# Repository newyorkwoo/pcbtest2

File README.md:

# aipcb：由 Claude 驅動的本機 EDA

用自然語言描述電路，Claude 撰寫 `design.yaml`。之後的原理圖、元件庫、物理式擺放、自動佈線、GND 鋪銅、SPICE 模擬、ERC/DRC、送廠審核與 Gerber 輸出，全部在本機自動完成，不需要連網。

## 需求
- KiCad 10（`/Applications/KiCad`），本系統使用它的 kicad-cli、元件庫與 libngspice
- Python 3.12 虛擬環境：`uv venv --python 3.12 .venv && uv pip install --python .venv/bin/python numpy pyyaml mcp PySide6-Essentials`

## 使用方式
| 方式 | 指令 |
|---|---|
| 在 Claude Code 中對話 | 在本資料夾開啟 Claude Code，`.mcp.json` 會自動載入 `aipcb` 工具，例如輸入「幫我設計…」或「審核 fm_radio 能否送廠」 |
| 桌面儀表板 | `.venv/bin/python -m aipcb gui fm_radio` |
| 命令列全流程 | `.venv/bin/python -m aipcb build fm_radio` |
| 送廠檔 | `.venv/bin/python -m aipcb fab fm_radio`（AI 審核 PASS 才放行；`--force` 僅限打樣） |

## 流程
`design.yaml` → 元件庫（含 AI 自訂元件）→ 規格驗證 → 原理圖 → ERC → 物理擺放（力導向 + 模擬退火 + 合法化）→ 佈線（雙層 A*、拆線重佈、GND 扇出）→ PCB → DRC（含鋪銅連通性的閉迴路修補）→ SPICE 模擬 → 設計檢查 → 預覽 → **Claude 審核** → 送廠檔

詳細的設計與審核規範見 `CLAUDE.md`。範例專案位於 `projects/fm_radio/`。

## 專案與電路圖
每次建置（`previews` 階段）都會自動更新各專案的 `README.md` 與 `docs/`：原理圖 PDF / SVG、PCB 3D 圖、檢查與審核摘要。

| 專案 | 說明 | 電路圖 |
|---|---|---|
| [fm_radio](projects/fm_radio/) | FM/藍牙口袋收音機（ESP32 + RDA5807M + PAM8302，USB-C 充電） | [PDF](projects/fm_radio/docs/fm_radio_schematic.pdf) · [SVG](projects/fm_radio/docs/schematic.svg) |
| [outdoor_hmi](projects/outdoor_hmi/) | Outdoor Hub Board 2：按鍵、旋鈕、SOS、震動馬達與 2.5 W 喇叭 | [PDF](projects/outdoor_hmi/docs/outdoor_hmi_schematic.pdf) · [SVG](projects/outdoor_hmi/docs/schematic.svg) |

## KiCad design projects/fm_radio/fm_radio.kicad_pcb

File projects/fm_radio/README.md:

# FM/BT Pocket Radio

> 本檔由 `python -m aipcb previews` 自動產生，請勿手動編輯；設計來源是 `design.yaml`。

| 項目 | 內容 |
|---|---|
| 板子尺寸 | 80 × 60 mm，2 層，厚 1.6 mm |
| 零件 / 網路 | 72 顆 / 49 個 |
| DRC | 0 錯誤、0 未連接 |
| 自動檢查 | 通過（error 0、warning 47） |
| SPICE 模擬 | 4/4 通過 |
| AI 審核 | **CONDITIONAL**（2026-11-13T12:46:02） |

## 電路圖 Schematic

可放大的向量版：[docs/fm_radio_schematic.pdf](docs/fm_radio_schematic.pdf)

## PCB

## AI 審核摘要

依上一版審核的建議完成換件：電源路徑改為 LTC4412 + AO3401A 理想二極體（拔除 USB 時的 9 ms 掉壓消失，模擬已驗證），CR1220 電池座改為 LCSC 有貨的 Keystone 3000，其餘缺料號的零件都補上已確認的 LCSC 料號。重建結果：ERC 0、DRC 0/0、幾何檢查通過、模擬 4/4 通過。PCB 可打樣。唯一未解決的是 U6 RDA5807M 在 LCSC 沒有料，需另外採購或手焊，所以仍判定「有條件通過」。

- **[WARNING] U6 RDA5807M 沒有 LCSC 料號**
- **[WARNING] 電池低於約 3.33 V 時 3.3 V 軌脫離穩壓（模擬 02）**
- **[WARNING] OLED 模組腳位順序因廠商而異**
- **[WARNING] VSYS 有 3.2 mm 走線縮到 0.2 mm**

完整審核內容：[out/review.md](out/review.md)

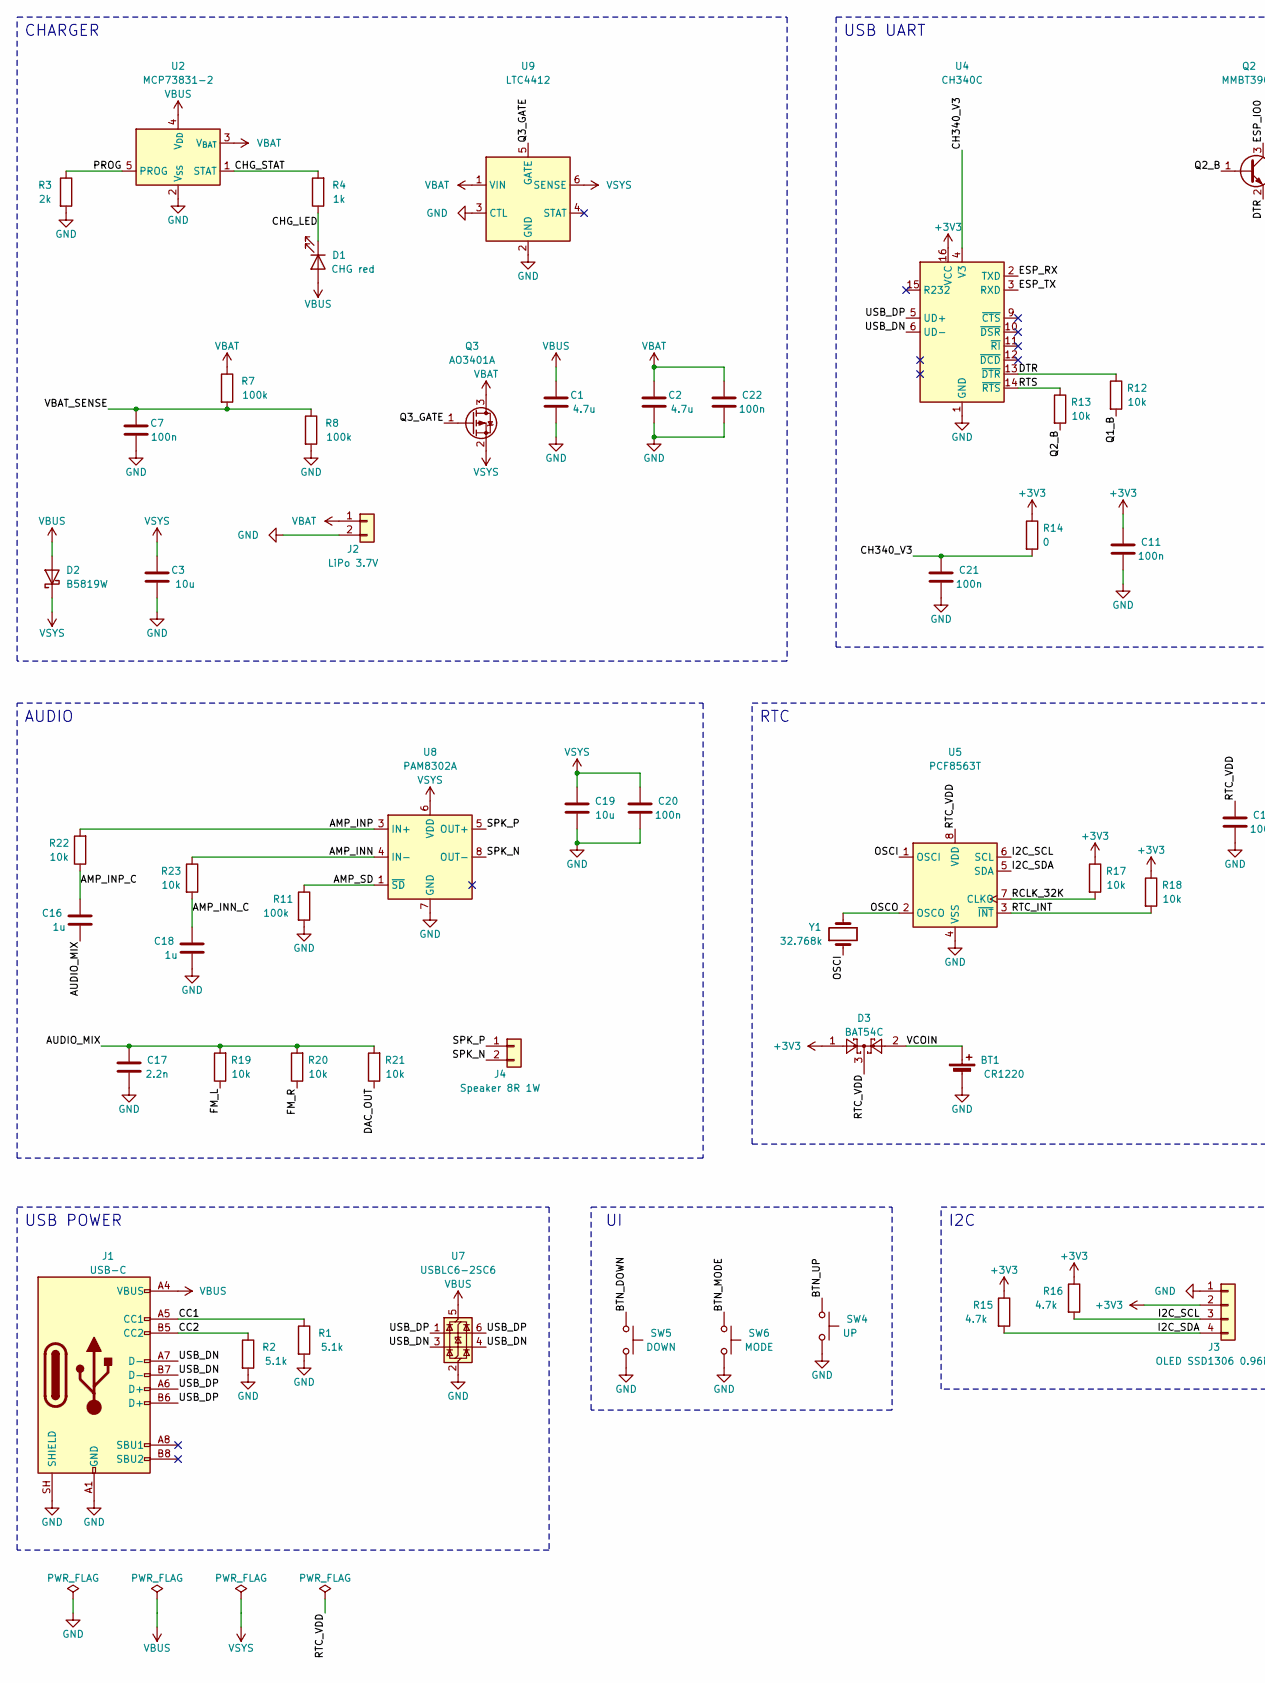
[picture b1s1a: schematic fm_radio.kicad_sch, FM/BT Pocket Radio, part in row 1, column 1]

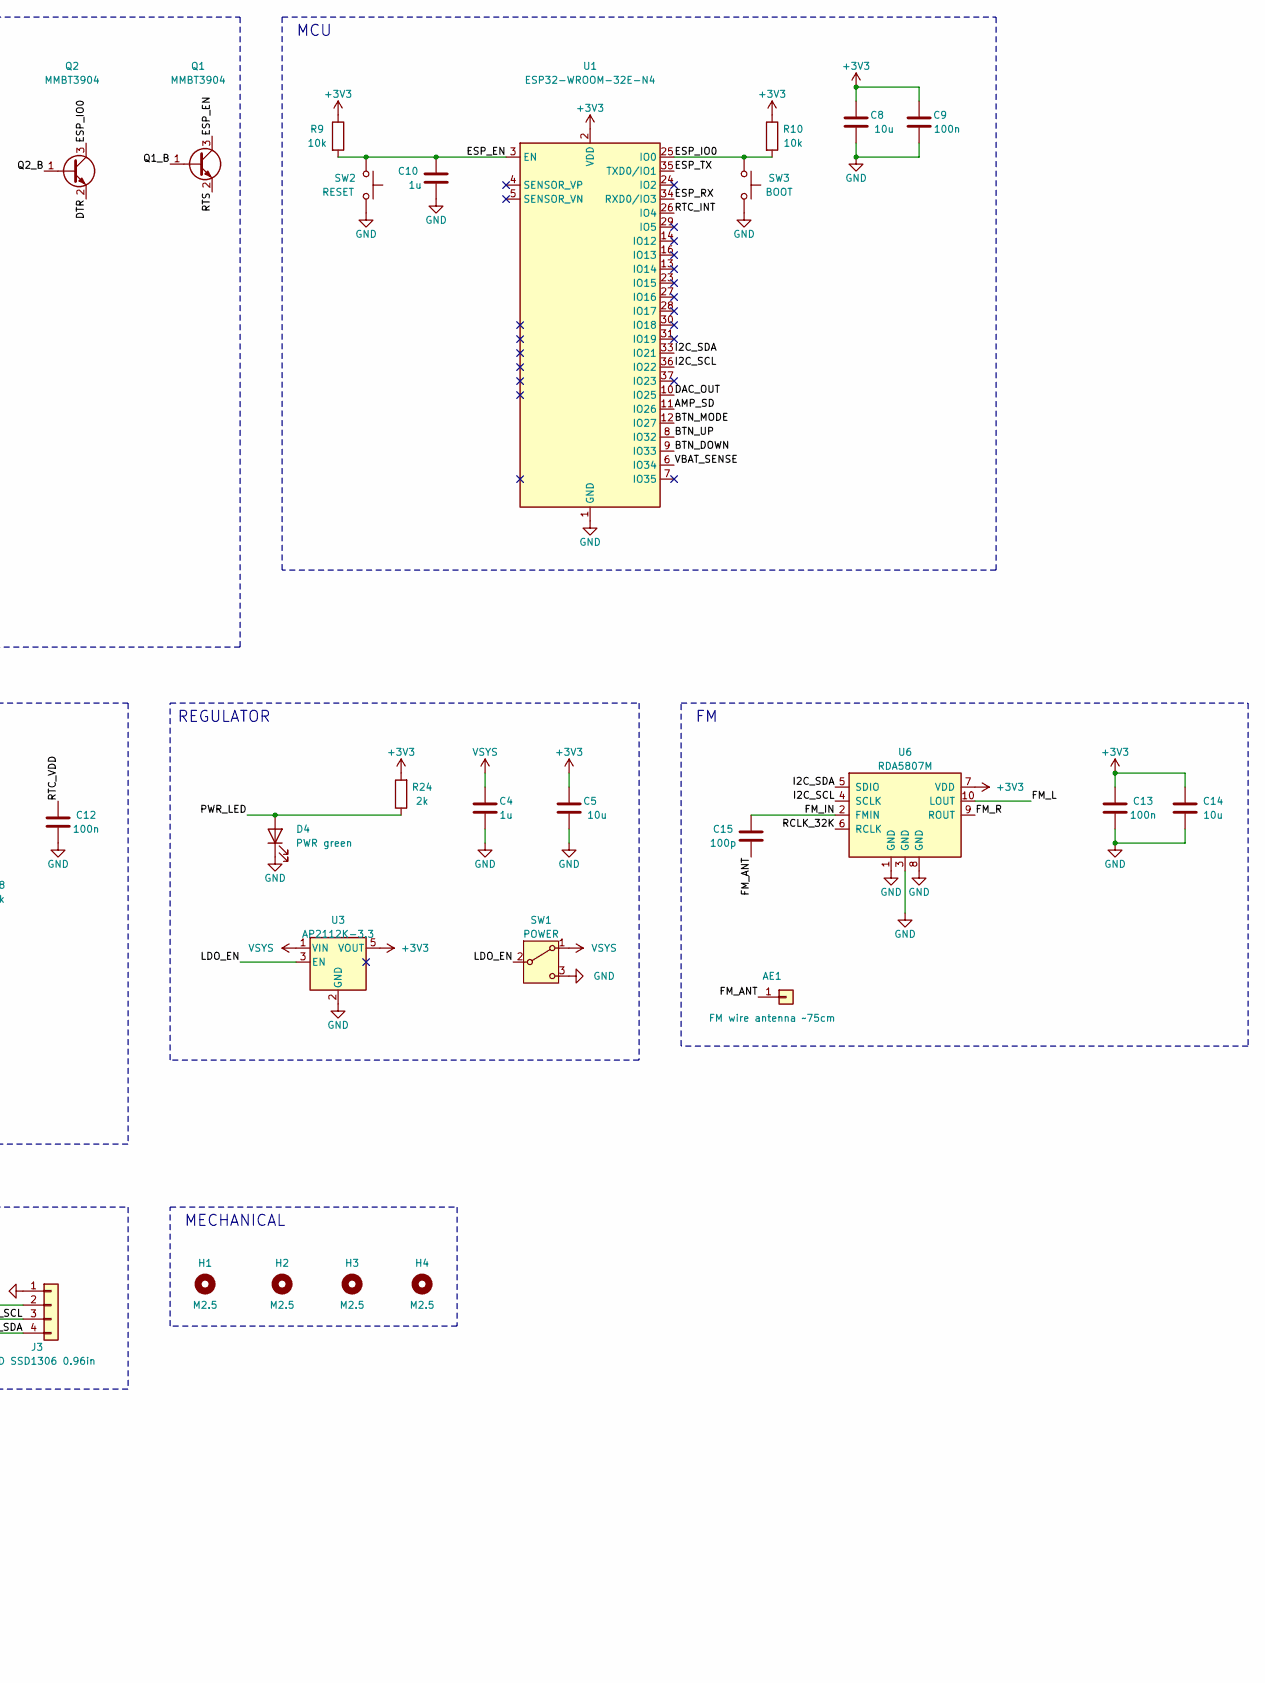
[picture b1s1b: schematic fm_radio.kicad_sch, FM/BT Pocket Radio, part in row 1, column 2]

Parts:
AE1: FM wire antenna ~75cm; SolderWire-0.127sqmm_1x01_D0.48mm_OD1mm; MPN wire
BT1: CR1220; BatteryHolder_Keystone_3000_1x12mm; MPN 3000; LCSC C238097
C1, C2: 4.7u; C_0603_1608Metric; MPN CL10A475KO8NNNC; LCSC C19666
C3, C5, C8, C14, C19: 10u; C_0805_2012Metric; MPN CL21A106KAYNNNE; LCSC C15850
C4, C10, C16, C18: 1u; C_0603_1608Metric; MPN CL10A105KB8NNNC; LCSC C15849
C7, C9, C11, C12, C13, C20, C21, C22: 100n; C_0603_1608Metric; MPN CC0603KRX7R9BB104; LCSC C14663
C15: 100p; C_0603_1608Metric; MPN 0603CG101J500NT; LCSC C14858
C17: 2.2n; C_0603_1608Metric; MPN CL10B222KB8NNNC; LCSC C1604
D1: CHG red; LED_0603_1608Metric; MPN KT-0603R; LCSC C2286
D2: B5819W; D_SOD-123; MPN B5819W; LCSC C8598
D3: BAT54C; SOT-23; MPN BAT54C,215; LCSC C37704
D4: PWR green; LED_0603_1608Metric; MPN KT-0603G; LCSC C12624
H1, H2, H3, H4: M2.5; MountingHole_2.7mm_M2.5
J1: USB-C; USB_C_Receptacle_HRO_TYPE-C-31-M-12; MPN TYPE-C-31-M-12; LCSC C165948
J2: LiPo 3.7V; JST_PH_S2B-PH-K_1x02_P2.00mm_Horizontal; MPN S2B-PH-K-S; LCSC C173752
J3: OLED SSD1306 0.96in; PinHeader_1x04_P2.54mm_Vertical; MPN PZ254V-11-04P; LCSC C2691448
J4: Speaker 8R 1W; JST_SH_SM02B-SRSS-TB_1x02-1MP_P1.00mm_Horizontal; MPN SM02B-SRSS-TB(LF)(SN); LCSC C160402
Q1, Q2: MMBT3904; SOT-23; MPN MMBT3904; LCSC C20526
Q3: AO3401A; SOT-23; MPN AO3401A; LCSC C15127
R1, R2: 5.1k; R_0603_1608Metric; MPN 0603WAF5101T5E; LCSC C23186
R3, R24: 2k; R_0603_1608Metric; MPN 0603WAF2001T5E; LCSC C22975
R4: 1k; R_0603_1608Metric; MPN 0603WAF1001T5E; LCSC C21190
R7, R8, R11: 100k; R_0603_1608Metric; MPN 0603WAF1003T5E; LCSC C25803
R9, R10, R12, R13, R17, R18, R19, R20, R21, R22, R23: 10k; R_0603_1608Metric; MPN 0603WAF1002T5E; LCSC C25804
R14: 0; R_0603_1608Metric; MPN 0603WAF0000T5E; LCSC C21189
R15, R16: 4.7k; R_0603_1608Metric; MPN 0603WAF4701T5E; LCSC C23162
SW1: POWER; SW_SPDT_PCM12; MPN PCM12SMTR; LCSC C221841
SW2: RESET; SW_SPST_B3U-1000P; MPN B3U-1000P; LCSC C231329
SW3: BOOT; SW_SPST_B3U-1000P; MPN B3U-1000P; LCSC C231329
SW4: UP; SW_SPST_PTS645Sx43SMTR92; MPN PTS645SM43SMTR92 LFS; LCSC C221880
SW5: DOWN; SW_SPST_PTS645Sx43SMTR92; MPN PTS645SM43SMTR92 LFS; LCSC C221880
SW6: MODE; SW_SPST_PTS645Sx43SMTR92; MPN PTS645SM43SMTR92 LFS; LCSC C221880
U1: ESP32-WROOM-32E-N4; ESP32-WROOM-32E; MPN ESP32-WROOM-32E-N4; LCSC C701341
U2: MCP73831-2; SOT-23-5; MPN MCP73831T-2ACI/OT; LCSC C424093
U3: AP2112K-3.3; SOT-23-5; MPN AP2112K-3.3TRG1; LCSC C51118
U4: CH340C; SOIC-16_3.9x9.9mm_P1.27mm; MPN CH340C; LCSC C84681
U5: PCF8563T; SOIC-8_3.9x4.9mm_P1.27mm; MPN PCF8563T/5; LCSC C7440
U6: RDA5807M; MSOP-10_3x3mm_P0.5mm; MPN RDA5807M
U7: USBLC6-2SC6; SOT-23-6; MPN USBLC6-2SC6; LCSC C7519
U8: PAM8302A; MSOP-8_3x3mm_P0.65mm; MPN PAM8302AASCR; LCSC C113367
U9: LTC4412; TSOT-23-6; MPN LTC4412ES6#TRPBF; LCSC C514442
Y1: 32.768k; Crystal_SMD_3215-2Pin_3.2x1.5mm; MPN Q13FC1350000400; LCSC C32346

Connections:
+3V3: C5.1, C8.1, C9.1, C11.1, C13.1, C14.1, D3.1, J3.2, R9.1, R10.1, R14.1, R15.1, R16.1, R17.1, R18.1, R24.2, U1.2 (VDD), U3.5 (VOUT), U4.16 (VCC), U6.7 (VDD)
/AMP_INN: R23.1, U8.4 (IN-)
/AMP_INN_C: C18.1, R23.2
/AMP_INP: R22.2, U8.3 (IN+)
/AMP_INP_C: C16.2, R22.1
/AMP_SD: R11.1, U1.11 (IO26), U8.1 (~SD)
/AUDIO_MIX: C16.1, C17.1, R19.2, R20.2, R21.2
/BTN_DOWN: SW5.1, U1.9 (IO33)
/BTN_MODE: SW6.1, U1.12 (IO27)
/BTN_UP: SW4.1, U1.8 (IO32)
/CC1: J1.A5 (CC1), R1.1
/CC2: J1.B5 (CC2), R2.1
/CH340_V3: C21.1, R14.2, U4.4 (V3)
/CHG_LED: D1.1 (K), R4.1
/CHG_STAT: R4.2, U2.1 (STAT)
/DAC_OUT: R21.1, U1.10 (IO25)
/DTR: Q2.2 (E), R12.1, U4.13 (~DTR)
/ESP_EN: C10.1, Q1.3 (C), R9.2, SW2.1, U1.3 (EN)
/ESP_IO0: Q2.3 (C), R10.2, SW3.1, U1.25 (IO0)
/ESP_RX: U1.34 (RXD0/IO3), U4.2 (TXD)
/ESP_TX: U1.35 (TXD0/IO1), U4.3 (RXD)
/FM_ANT: AE1.1, C15.1
/FM_IN: C15.2, U6.2 (FMIN)
/FM_L: R19.1, U6.10 (LOUT)
/FM_R: R20.1, U6.9 (ROUT)
/I2C_SCL: J3.3, R16.2, U1.36 (IO22), U5.6 (SCL), U6.4 (SCLK)
/I2C_SDA: J3.4, R15.2, U1.33 (IO21), U5.5 (SDA), U6.5 (SDIO)
/LDO_EN: SW1.2 (B), U3.3 (EN)
/OSCI: U5.1 (OSCI), Y1.1
/OSCO: U5.2 (OSCO), Y1.2
/PROG: R3.1, U2.5 (PROG)
/PWR_LED: D4.2 (A), R24.1
/Q1_B: Q1.1 (B), R12.2
/Q2_B: Q2.1 (B), R13.2
/Q3_GATE: Q3.1 (G), U9.5 (GATE)
/RCLK_32K: R17.2, U5.7 (CLKO), U6.6 (RCLK)
/RTC_INT: R18.2, U1.26 (IO4), U5.3 (~INT)
/RTC_VDD: C12.1, D3.3, U5.8 (VDD)
/RTS: Q1.2 (E), R13.1, U4.14 (~RTS)
/SPK_N: J4.2, U8.8 (OUT-)
/SPK_P: J4.1, U8.5 (OUT+)
/USB_DN: J1.A7 (D-), J1.B7 (D-), U4.6 (UD-), U7.3 (I/O2), U7.4 (I/O2)
/USB_DP: J1.A6 (D+), J1.B6 (D+), U4.5 (UD+), U7.1 (I/O1), U7.6 (I/O1)
/VBAT_SENSE: C7.1, R7.2, R8.1, U1.6 (IO34)
/VCOIN: BT1.1 (+), D3.2
GND: BT1.2 (-), C1.2, C2.2, C3.2, C4.2, C5.2, C7.2, C8.2, C9.2, C10.2, C11.2, C12.2, C13.2, C14.2, C17.2, C18.2, C19.2, C20.2, C21.2, C22.2, D4.1 (K), J1.A1 (GND), J1.A12 (GND), J1.B1 (GND), J1.B12 (GND), J1.SH (SHIELD), J2.2, J3.1, R1.2, R2.2, R3.2, R8.2, R11.2, SW1.3 (C), SW2.2, SW3.2, SW4.2, SW5.2, SW6.2, U1.1 (GND), U1.15 (GND), U1.38 (GND), U1.39 (GND), U2.2 (V_{SS}), U3.2 (GND), U4.1 (GND), U5.4 (VSS), U6.1 (GND), U6.3 (GND), U6.8 (GND), U7.2 (GND), U8.7 (GND), U9.2 (GND), U9.3 (CTL)
VBAT: C2.1, C22.1, J2.1, Q3.3 (D), R7.1, U2.3 (V_{BAT}), U9.1 (VIN)
VBUS: C1.1, D1.2 (A), D2.2 (A), J1.A4 (VBUS), J1.A9 (VBUS), J1.B4 (VBUS), J1.B9 (VBUS), U2.4 (V_{DD}), U7.5 (VBUS)
VSYS: C3.1, C4.1, C19.1, C20.1, D2.1 (K), Q3.2 (S), SW1.1 (A), U3.1 (VIN), U8.6 (VDD), U9.6 (SENSE)

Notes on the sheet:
CHARGER
USB UART
MCU
AUDIO
RTC
REGULATOR
USB POWER
I2C
MECHANICAL

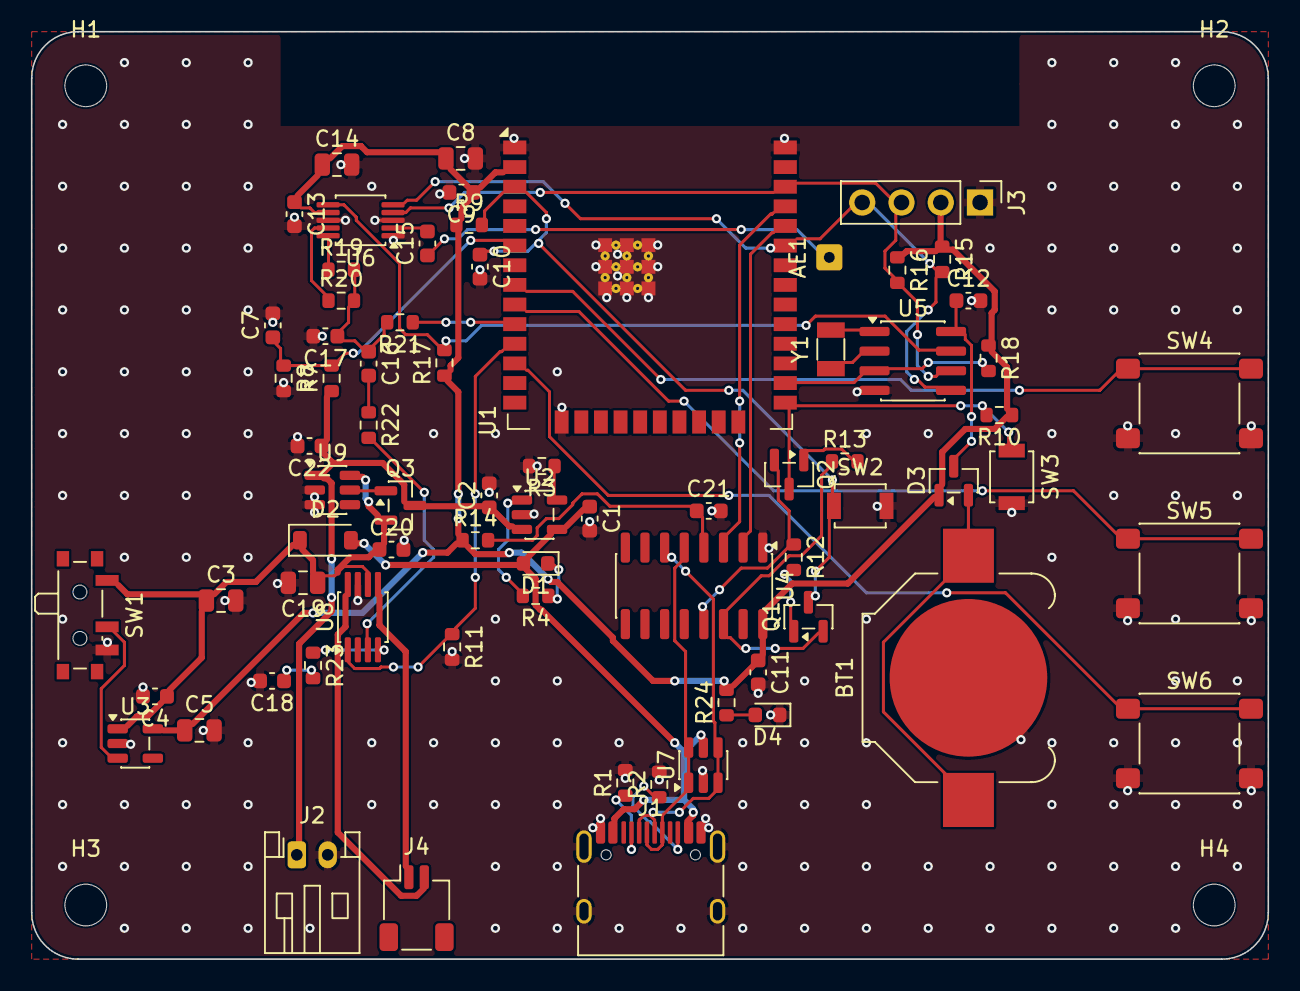
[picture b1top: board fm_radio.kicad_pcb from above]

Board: 2 copper layers, 80.0 x 60.0 mm, 76 parts (0 on the bottom side), 49 nets.

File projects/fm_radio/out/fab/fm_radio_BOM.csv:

Comment,Designator,Footprint,LCSC Part #,Qty,MPN,Manufacturer,Description
FM wire antenna ~75cm,AE1,SolderWire-0.127sqmm_1x01_D0.48mm_OD1mm,,1,wire,,
CR1220,BT1,Battery_Panasonic_CR1220-VCN_Vertical_CircularHoles,,1,CR1220-VCN,Panasonic,
4.7u,"C1,C2",C_0603_1608Metric,C19666,2,CL10A475KO8NNNC,,
100p,C15,C_0603_1608Metric,C14858,1,0603CG101J500NT,,
2.2n,C17,C_0603_1608Metric,C1604,1,CL10B222KB8NNNC,,mixer RC low-pass ~22 kHz
10u,"C3,C5,C8,C14,C19",C_0805_2012Metric,C15850,5,CL21A106KAYNNNE,,
1u,"C4,C10,C16,C18",C_0603_1608Metric,C15849,4,CL10A105KB8NNNC,,
100n,"C7,C9,C11,C12,C13,C20,C21",C_0603_1608Metric,C14663,7,CC0603KRX7R9BB104,,
CHG red,D1,LED_0603_1608Metric,C2286,1,KT-0603R,,
B5819W,D2,D_SOD-123,C8598,1,B5819W,,
BAT54C,D3,SOT-23,,1,BAT54C,,
PWR green,D4,LED_0603_1608Metric,C12624,1,KT-0603G,,
USB-C,J1,USB_C_Receptacle_HRO_TYPE-C-31-M-12,C165948,1,TYPE-C-31-M-12,Korean Hroparts,
LiPo 3.7V,J2,JST_PH_S2B-PH-K_1x02_P2.00mm_Horizontal,C173752,1,S2B-PH-K-S,JST,pin1 = +BAT
OLED SSD1306 0.96in,J3,PinHeader_1x04_P2.54mm_Vertical,C2932,1,PZ254V-11-04P,,GND VCC SCL SDA
Speaker 8R 1W,J4,JST_SH_SM02B-SRSS-TB_1x02-1MP_P1.00mm_Horizontal,,1,SM02B-SRSS-TB(LF)(SN),JST,JST-SH 1.0 mm: deliberately different from the battery JST-PH so the cells cannot be swapped in
MMBT3904,"Q1,Q2",SOT-23,C20526,2,MMBT3904,,
AO3401A,Q3,SOT-23,C15127,1,AO3401A,AOS,
5.1k,"R1,R2",R_0603_1608Metric,C23186,2,0603WAF5101T5E,,
0,R14,R_0603_1608Metric,C21189,1,0603WAF0000T5E,,ties CH340C V3 to VCC (3.3 V operation)
4.7k,"R15,R16",R_0603_1608Metric,C23162,2,0603WAF4701T5E,,
2k,"R3,R24",R_0603_1608Metric,C22975,2,0603WAF2001T5E,,PROG: Ichg = 1000/R = 500 mA
1k,R4,R_0603_1608Metric,C21190,1,0603WAF1001T5E,,
10k,"R5,R9,R10,R12,R13,R17,R18,R19,R20,R21,R22,R23",R_0603_1608Metric,C25804,12,0603WAF1002T5E,,Q3 gate pull-down: 10k so VBUS bleeds fast after unplug (sim 01)
100k,"R7,R8,R11",R_0603_1608Metric,C25803,3,0603WAF1003T5E,,
POWER,SW1,SW_SPDT_PCM12,C221841,1,PCM12SMTR,C&K,
RESET,SW2,SW_SPST_B3U-1000P,C231329,1,B3U-1000P,Omron,
BOOT,SW3,SW_SPST_B3U-1000P,C231329,1,B3U-1000P,Omron,
UP,SW4,SW_SPST_PTS645Sx43SMTR92,,1,PTS645SM43SMTR92,C&K,
DOWN,SW5,SW_SPST_PTS645Sx43SMTR92,,1,PTS645SM43SMTR92,C&K,
MODE,SW6,SW_SPST_PTS645Sx43SMTR92,,1,PTS645SM43SMTR92,C&K,
ESP32-WROOM-32E-N4,U1,ESP32-WROOM-32E,C701341,1,ESP32-WROOM-32E-N4,Espressif,
MCP73831-2,U2,SOT-23-5,C424093,1,MCP73831T-2ACI/OT,Microchip,
AP2112K-3.3,U3,SOT-23-5,C51118,1,AP2112K-3.3TRG1,Diodes Inc,
CH340C,U4,SOIC-16_3.9x9.9mm_P1.27mm,C84681,1,CH340C,WCH,
PCF8563T,U5,SOIC-8_3.9x4.9mm_P1.27mm,C7440,1,PCF8563T/5,NXP,
RDA5807M,U6,MSOP-10_3x3mm_P0.5mm,,1,RDA5807M,RDA Microelectronics,
USBLC6-2SC6,U7,SOT-23-6,C7519,1,USBLC6-2SC6,STMicroelectronics,
PAM8302A,U8,MSOP-8_3x3mm_P0.65mm,C113367,1,PAM8302AADCR,Diodes Inc,
32.768k,Y1,Crystal_SMD_3215-2Pin_3.2x1.5mm,C32346,1,Q13FC1350000400,,

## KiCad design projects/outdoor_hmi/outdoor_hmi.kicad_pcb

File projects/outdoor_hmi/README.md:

# Outdoor Hub — HMI & Alarm Board (Board 2)

> 本檔由 `python -m aipcb previews` 自動產生，請勿手動編輯；設計來源是 `design.yaml`。

| 項目 | 內容 |
|---|---|
| 板子尺寸 | 80 × 48 mm，2 層，厚 1.0 mm |
| 零件 / 網路 | 96 顆 / 59 個 |
| DRC | 0 錯誤、0 未連接 |
| 自動檢查 | 通過（error 0、warning 68） |
| SPICE 模擬 | 4/4 通過 |
| AI 審核 | **CONDITIONAL**（2026-11-13T12:46:02） |

## 電路圖 Schematic

可放大的向量版：[docs/outdoor_hmi_schematic.pdf](docs/outdoor_hmi_schematic.pdf)

## PCB

## AI 審核摘要

用目前引擎完整跑過一次流程（--keep，零件位置不變）：ERC 0、DRC 0/0、幾何鋪銅檢查通過、模擬全部通過。上一版的阻擋項「兩個 AI 繪製的封裝」已用原廠圖獨立核對，全部符合。剩下唯一的條件是 EC12D 固定腳插入橢圓槽的實體試裝；試裝 OK 就可以改判 PASS。

- **[WARNING] 剩下一項：實體試裝（EC12D 固定腳槽）**
- **[WARNING] FPC 連接器沒有 LCSC 庫存**
- **[WARNING] SOS 硬體 3 秒判定的誤差（未變）**

完整審核內容：[out/review.md](out/review.md)

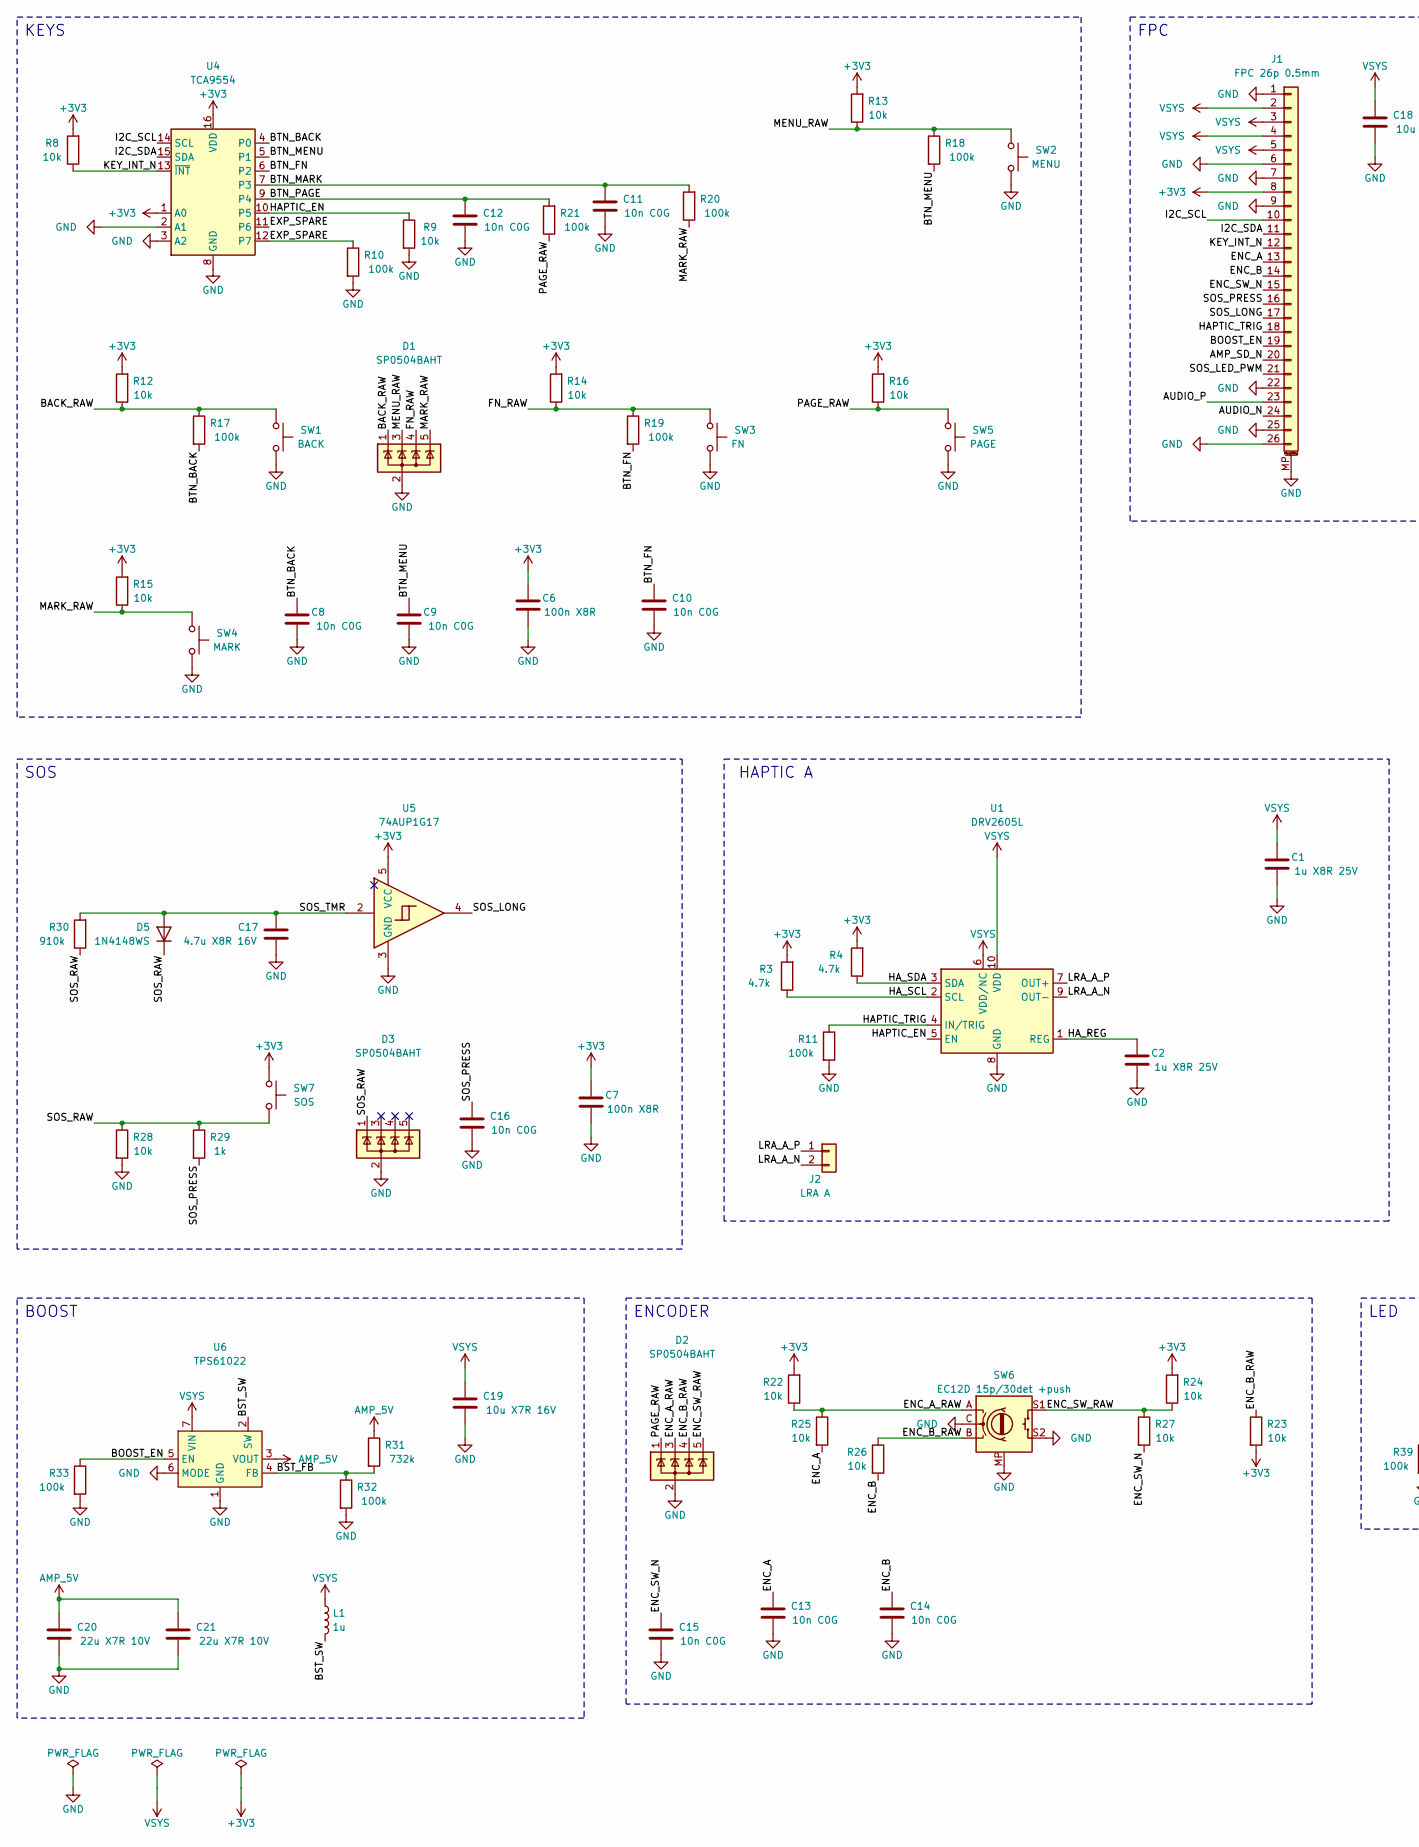
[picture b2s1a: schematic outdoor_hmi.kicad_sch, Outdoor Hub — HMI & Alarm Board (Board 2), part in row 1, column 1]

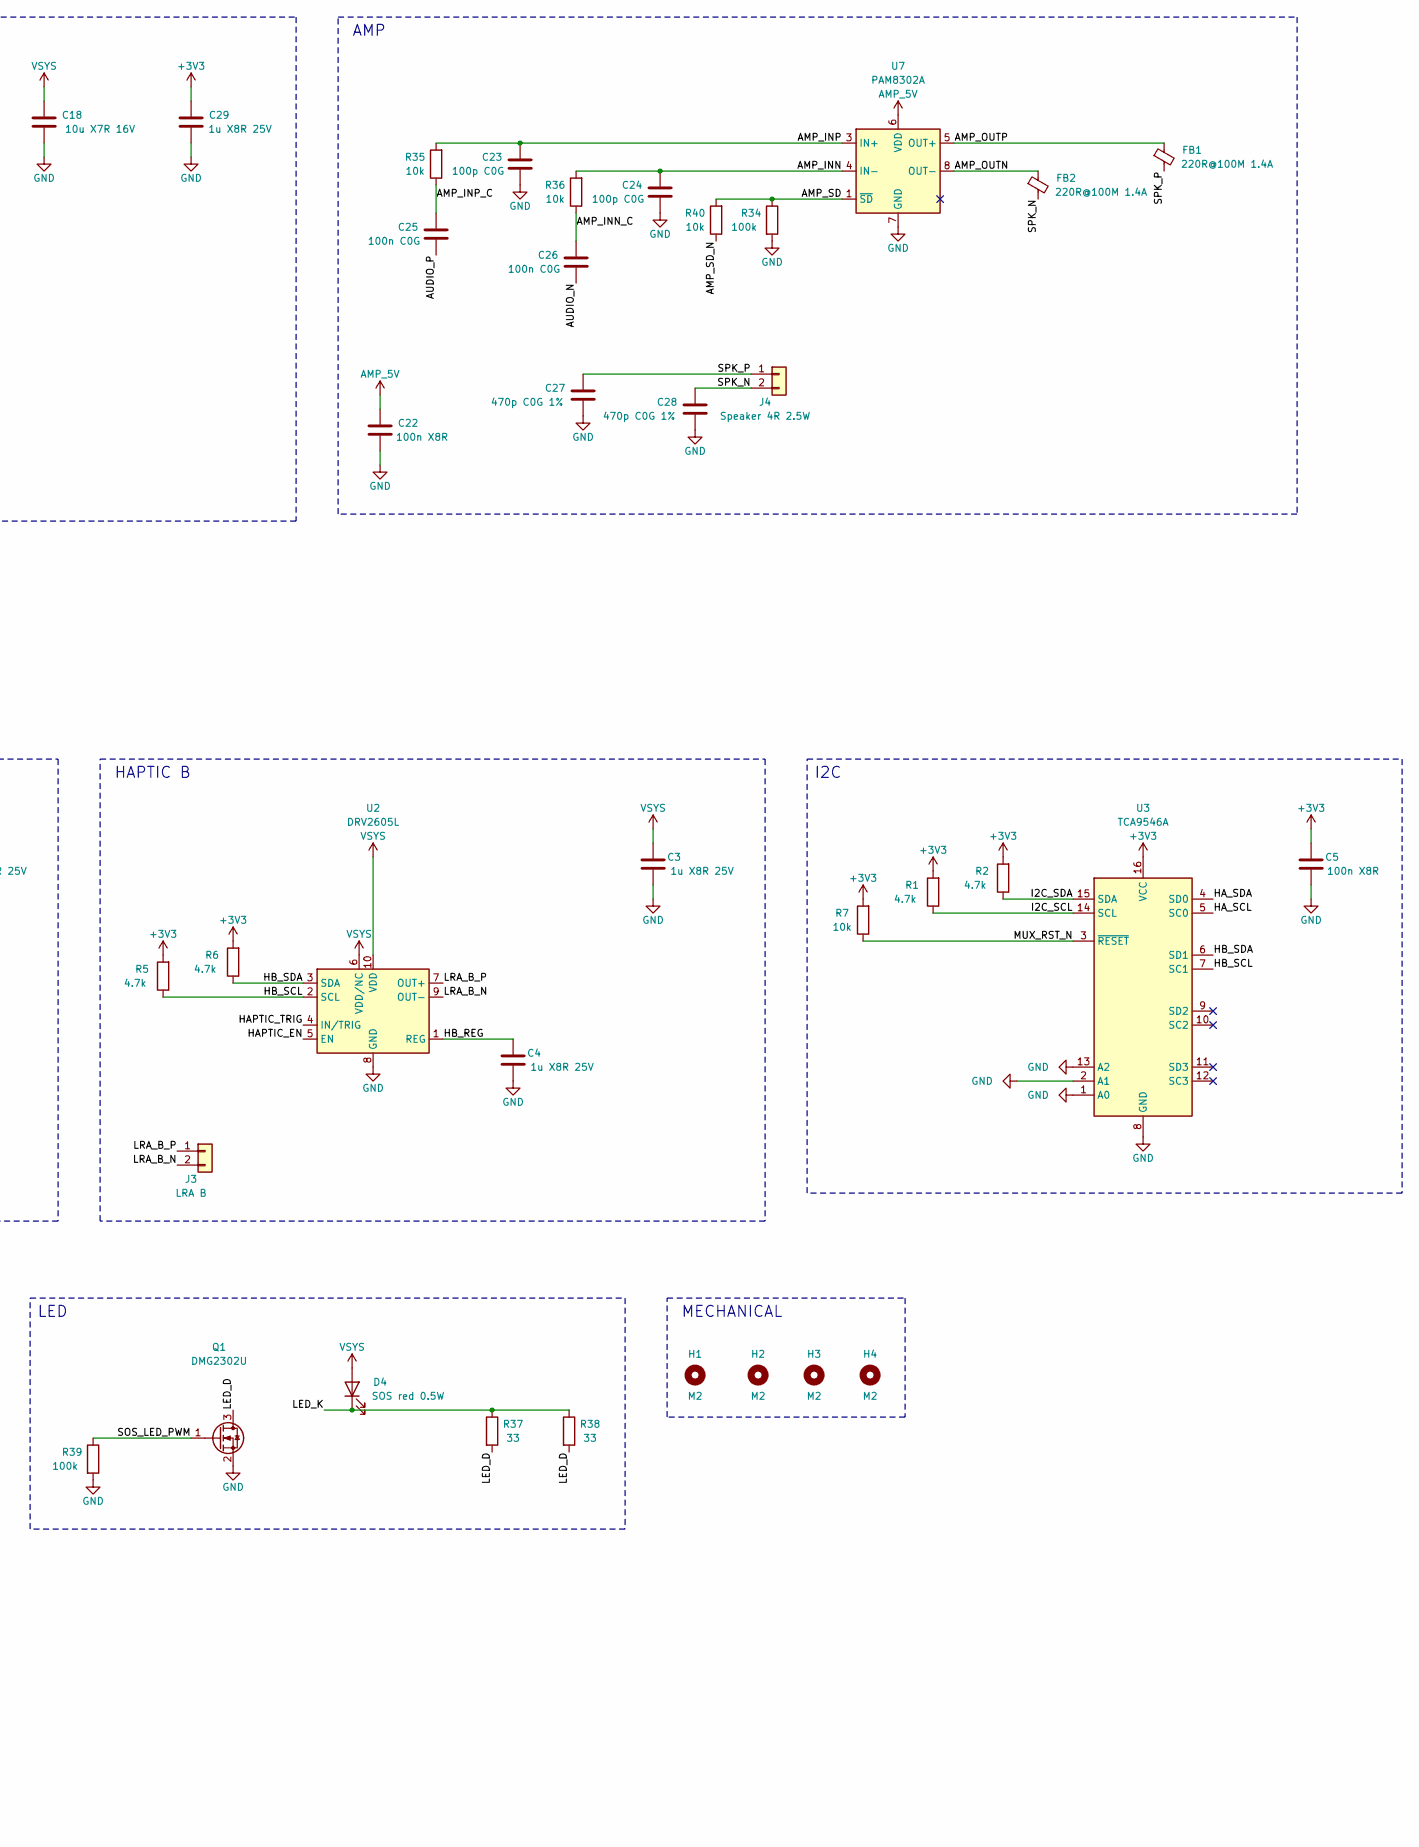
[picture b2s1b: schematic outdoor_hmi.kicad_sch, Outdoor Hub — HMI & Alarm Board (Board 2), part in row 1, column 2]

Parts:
C1, C2, C3, C4, C29: 1u X8R 25V; C_0805_2012Metric; MPN CGA4J1X8R1E105K125AC
C5, C6, C7, C22: 100n X8R; C_0603_1608Metric; MPN CGA3E2X8R1E104K080AA
C8, C9, C10, C11, C12, C13, C14, C15, C16: 10n C0G; C_0603_1608Metric; MPN GCM1885C1H103JA16D
C17: 4.7u X8R 16V; C_1206_3216Metric; MPN CGA5L3X8R1C475K160AE
C18, C19: 10u X7R 16V; C_1206_3216Metric; MPN CGA5L1X7R1C106K160AC
C20, C21: 22u X7R 10V; C_1206_3216Metric; MPN GCM31CR71A226KE02L; LCSC C126598
C23, C24: 100p C0G; C_0603_1608Metric; MPN GCM1885C1H101JA16D
C25, C26: 100n C0G; C_1206_3216Metric; MPN GRM3195C1H104JA05D
C27, C28: 470p C0G 1%; C_0603_1608Metric; MPN GCM1885C1H471FA16D; LCSC C3907937
D1, D2, D3: SP0504BAHT; SOT-23-5; MPN SP0504BAHTG; LCSC C10675
D4: SOS red 0.5W; LED_Broadcom_2835_DFN2; MPN CSMW-LR00-ATV0E
D5: 1N4148WS; D_SOD-323; MPN 1N4148WS-7-F; LCSC C60580
FB1, FB2: 220R@100M 1.4A; L_0603_1608Metric; MPN BLM18PG221SN1D; LCSC C80165
H1, H2, H3, H4: M2; MountingHole_2.2mm_M2
J1: FPC 26p 0.5mm; Hirose_FH12-26S-0.5SH_1x26-1MP_P0.50mm_Horizontal; MPN FH12-26S-0.5SH(55)
J2: LRA A; Molex_PicoBlade_53261-0271_1x02-1MP_P1.25mm_Horizontal; MPN 53261-0271
J3: LRA B; Molex_PicoBlade_53261-0271_1x02-1MP_P1.25mm_Horizontal; MPN 53261-0271
J4: Speaker 4R 2.5W; Molex_PicoBlade_53261-0271_1x02-1MP_P1.25mm_Horizontal; MPN 53261-0271
L1: 1u; L_Coilcraft_XAL4020-XXX; MPN XAL4020-102MEC
Q1: DMG2302U; SOT-23; MPN DMG2302U-7; LCSC C96613
R1, R2, R3, R4, R5, R6: 4.7k; R_0603_1608Metric; MPN AC0603FR-074K7L
R7, R8, R9, R12, R13, R14, R15, R16, R22, R23, R24, R25, R26, R27, R28, R35, R36, R40: 10k; R_0603_1608Metric; MPN AC0603FR-0710KL
R10, R11, R17, R18, R19, R20, R21, R32, R33, R34, R39: 100k; R_0603_1608Metric; MPN AC0603FR-07100KL
R29: 1k; R_0603_1608Metric; MPN AC0603FR-071KL
R30: 910k; R_0603_1608Metric; MPN AC0603FR-07910KL
R31: 732k; R_0603_1608Metric; MPN AC0603FR-07732KL
R37, R38: 33; R_1206_3216Metric; MPN AC1206FR-0733RL
SW1: BACK; SW_Push_1P1T_NO_CK_KSC7xxJ; MPN KSC741J LFS; LCSC C221766
SW2: MENU; SW_Push_1P1T_NO_CK_KSC7xxJ; MPN KSC741J LFS; LCSC C221766
SW3: FN; SW_Push_1P1T_NO_CK_KSC7xxJ; MPN KSC741J LFS; LCSC C221766
SW4: MARK; SW_Push_1P1T_NO_CK_KSC7xxJ; MPN KSC741J LFS; LCSC C221766
SW5: PAGE; SW_Push_1P1T_NO_CK_KSC7xxJ; MPN KSC741J LFS; LCSC C221766
SW6: EC12D 15p/30det +push; Alps_EC12D_Switch_Vertical; MPN EC12D1524403; LCSC C112349
SW7: SOS; SW_Push_1P1T_NO_CK_KSC7xxJ; MPN KSC741J LFS; LCSC C221766
U1, U2: DRV2605L; TSSOP-10_3x3mm_P0.5mm; MPN DRV2605LDGSR; LCSC C527464
U3: TCA9546A; TSSOP-16_4.4x5mm_P0.65mm; MPN TCA9546APWR; LCSC C201653
U4: TCA9554; TSSOP-16_4.4x5mm_P0.65mm; MPN TCA9554PWR; LCSC C477924
U5: 74AUP1G17; SOT-353_SC-70-5; MPN SN74AUP1G17DCKR; LCSC C2652099
U6: TPS61022; Texas_RWU0007A_VQFN-7_2x2mm_P0.5mm; MPN TPS61022RWUR; LCSC C915088
U7: PAM8302A; MSOP-8_3x3mm_P0.65mm; MPN PAM8302AASCR; LCSC C113367

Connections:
+3V3: C5.1, C6.1, C7.1, C29.1, J1.8, R1.2, R2.2, R3.2, R4.2, R5.2, R6.2, R7.2, R8.2, R12.2, R13.2, R14.2, R15.2, R16.2, R22.2, R23.2, R24.2, SW7.1, U3.16 (VCC), U4.1 (A0), U4.16 (VDD), U5.5 (VCC)
/AMP_INN: C24.1, R36.2, U7.4 (IN-)
/AMP_INN_C: C26.2, R36.1
/AMP_INP: C23.1, R35.2, U7.3 (IN+)
/AMP_INP_C: C25.2, R35.1
/AMP_OUTN: FB2.1, U7.8 (OUT-)
/AMP_OUTP: FB1.1, U7.5 (OUT+)
/AMP_SD: R34.1, R40.2, U7.1 (~SD)
/AMP_SD_N: J1.20, R40.1
/AUDIO_N: C26.1, J1.24
/AUDIO_P: C25.1, J1.23
/BACK_RAW: D1.1 (K), R12.1, R17.1, SW1.1
/BOOST_EN: J1.19, R33.1, U6.5 (EN)
/BST_FB: R31.2, R32.1, U6.4 (FB)
/BST_SW: L1.2, U6.2 (SW)
/BTN_BACK: C8.1, R17.2, U4.4 (P0)
/BTN_FN: C10.1, R19.2, U4.6 (P2)
/BTN_MARK: C11.1, R20.2, U4.7 (P3)
/BTN_MENU: C9.1, R18.2, U4.5 (P1)
/BTN_PAGE: C12.1, R21.2, U4.9 (P4)
/ENC_A: C13.1, J1.13, R25.2
/ENC_A_RAW: D2.3 (K), R22.1, R25.1, SW6.A
/ENC_B: C14.1, J1.14, R26.2
/ENC_B_RAW: D2.4 (K), R23.1, R26.1, SW6.B
/ENC_SW_N: C15.1, J1.15, R27.2
/ENC_SW_RAW: D2.5 (K), R24.1, R27.1, SW6.S1
/EXP_SPARE: R10.1, U4.11 (P6), U4.12 (P7)
/FN_RAW: D1.4 (K), R14.1, R19.1, SW3.1
/HAPTIC_EN: R9.1, U1.5 (EN), U2.5 (EN), U4.10 (P5)
/HAPTIC_TRIG: J1.18, R11.1, U1.4 (IN/TRIG), U2.4 (IN/TRIG)
/HA_REG: C2.1, U1.1 (REG)
/HA_SCL: R3.1, U1.2 (SCL), U3.5 (SC0)
/HA_SDA: R4.1, U1.3 (SDA), U3.4 (SD0)
/HB_REG: C4.1, U2.1 (REG)
/HB_SCL: R5.1, U2.2 (SCL), U3.7 (SC1)
/HB_SDA: R6.1, U2.3 (SDA), U3.6 (SD1)
/I2C_SCL: J1.10, R1.1, U3.14 (SCL), U4.14 (SCL)
/I2C_SDA: J1.11, R2.1, U3.15 (SDA), U4.15 (SDA)
/KEY_INT_N: J1.12, R8.1, U4.13 (~INT)
/LED_D: Q1.3 (D), R37.2, R38.2
/LED_K: D4.1 (K), R37.1, R38.1
/LRA_A_N: J2.2, U1.9 (OUT-)
/LRA_A_P: J2.1, U1.7 (OUT+)
/LRA_B_N: J3.2, U2.9 (OUT-)
/LRA_B_P: J3.1, U2.7 (OUT+)
/MARK_RAW: D1.5 (K), R15.1, R20.1, SW4.1
/MENU_RAW: D1.3 (K), R13.1, R18.1, SW2.1
/MUX_RST_N: R7.1, U3.3 (~RESET)
/PAGE_RAW: D2.1 (K), R16.1, R21.1, SW5.1
/SOS_LED_PWM: J1.21, Q1.1 (G), R39.1
/SOS_LONG: J1.17, U5.4
/SOS_PRESS: C16.1, J1.16, R29.2
/SOS_RAW: D3.1 (K), D5.1 (K), R28.1, R29.1, R30.1, SW7.2
/SOS_TMR: C17.1, D5.2 (A), R30.2, U5.2
/SPK_N: C28.1, FB2.2, J4.2
/SPK_P: C27.1, FB1.2, J4.1
AMP_5V: C20.1, C21.1, C22.1, R31.1, U6.3 (VOUT), U7.6 (VDD)
GND: C1.2, C2.2, C3.2, C4.2, C5.2, C6.2, C7.2, C8.2, C9.2, C10.2, C11.2, C12.2, C13.2, C14.2, C15.2, C16.2, C17.2, C18.2, C19.2, C20.2, C21.2, C22.2, C23.2, C24.2, C27.2, C28.2, C29.2, D1.2 (A), D2.2 (A), D3.2 (A), J1.1, J1.6, J1.7, J1.9, J1.22, J1.25, J1.26, J1.MP (MountPin), Q1.2 (S), R9.2, R10.2, R11.2, R28.2, R32.2, R33.2, R34.2, R39.2, SW1.2, SW2.2, SW3.2, SW4.2, SW5.2, SW6.C, SW6.MP, SW6.S2, U1.8 (GND), U2.8 (GND), U3.1 (A0), U3.2 (A1), U3.8 (GND), U3.13 (A2), U4.2 (A1), U4.3 (A2), U4.8 (GND), U5.3 (GND), U6.1 (GND), U6.6 (MODE), U7.7 (GND)
VSYS: C1.1, C3.1, C18.1, C19.1, D4.2 (A), J1.2, J1.3, J1.4, J1.5, L1.1, U1.6 (VDD/NC), U1.10 (VDD), U2.6 (VDD/NC), U2.10 (VDD), U6.7 (VIN)

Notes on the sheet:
KEYS
FPC
AMP
SOS
HAPTIC A
HAPTIC B
I2C
BOOST
ENCODER
LED
MECHANICAL

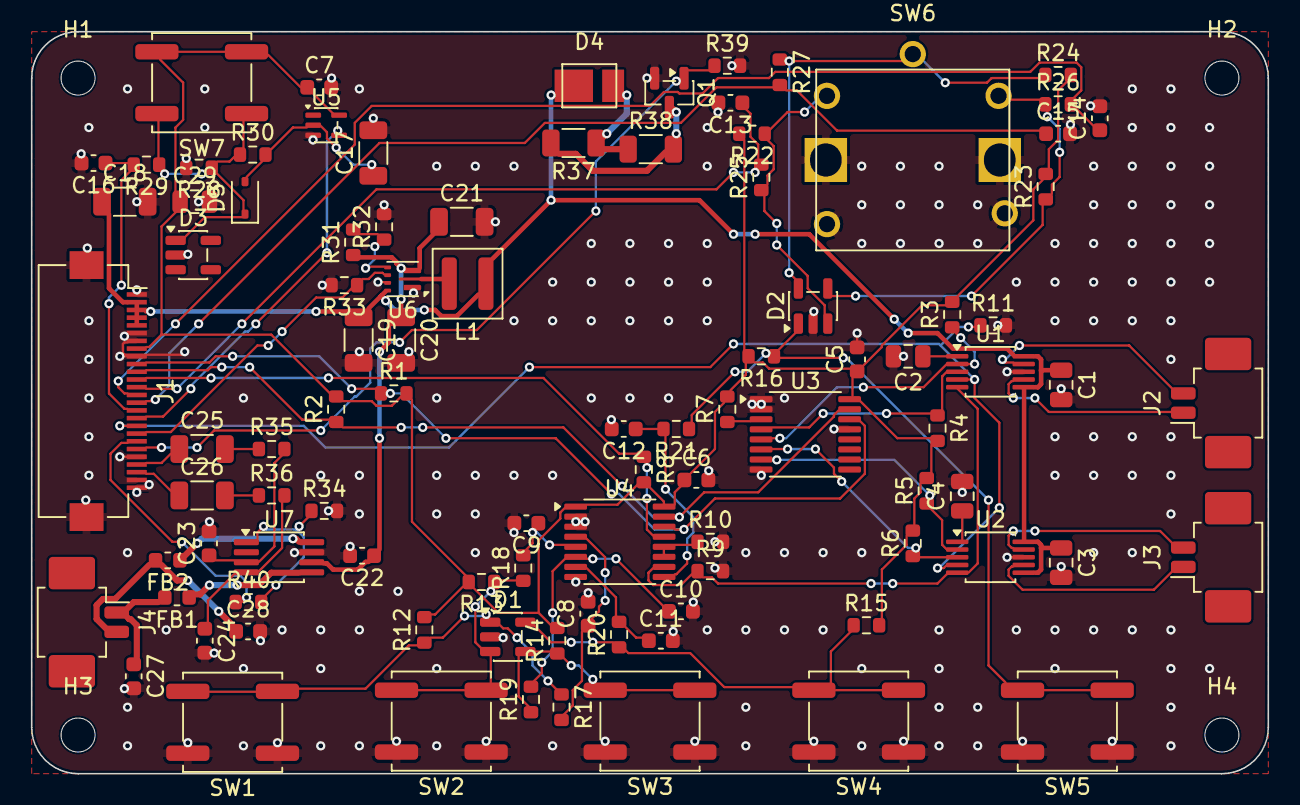
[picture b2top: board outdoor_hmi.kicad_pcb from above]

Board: 2 copper layers, 80.0 x 48.0 mm, 100 parts (0 on the bottom side), 59 nets.

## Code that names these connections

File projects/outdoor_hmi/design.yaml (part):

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  I2C (single bus, 3.3 V, 400 kHz)
  - 0x21 TCA9554 key expander (A0=1). 0x70 TCA9546A I2C switch (A2..A0=0).
  - The two DRV2605L share the fixed address 0x5A, so each sits on its own TCA9546A channel
    (CH0 = haptic A, CH1 = haptic B). Both IN/TRIG pins share HAPTIC_TRIG so the AP fires both LRAs
    in the same edge (symmetric vibration); both EN pins share HAPTIC_EN (expander P5).
  - Upstream pull-ups R1/R2 4.7k are fitted here; DNP them if Board 1 already pulls the bus up.

  Keys
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    inside the 200 mA DC rating (sim 03).

  Haptics: 2 x DRV2605L (closed-loop LRA resonance tracking + auto-calibration, compensates temperature drift),
    VDD = VSYS (2..5.2 V), REG and VDD 1 uF each; LRA leads on JST-SH 2-pin.

  Audio (2.5 W / 4 ohm alarm & radio speaker)
  - A 3.0-4.35 V cell cannot reach 2.5 W into 4 ohm BTL without a boost (~1.3 W max), so TPS61022 boosts
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  - TPS61022 verified against TI SLVSF19-class datasheet: pins 1 GND 2 SW 3 VOUT 4 FB 5 EN 6 MODE 7 VIN;
    VREF 585/600/615 mV -> AMP_5V 4.87..5.12 V; MODE low = auto PFM; L 0.33-2.9 uH; COUT >= 10 uF effective
    (IOUT <= 1.5 A); CIN >= 4.7 uF effective; R2 < 300k. 732k/100k is TI's own typical-application divider.
  - Differential input AUDIO_P/N from the AP codec: 100 nF C0G DC block -> 10k -> 100 pF C0G at the amp pins.
    RC low-pass 159 kHz per leg: >60 dB ideal rejection of FRS 467 MHz that couples onto the FPC pair (sim 02).
    High-pass ~80 Hz (protects the small speaker and kills plop).
  - Filterless outputs: ferrite bead + 470 pF C0G per leg against EMI into the GNSS/DAB antennas.
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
